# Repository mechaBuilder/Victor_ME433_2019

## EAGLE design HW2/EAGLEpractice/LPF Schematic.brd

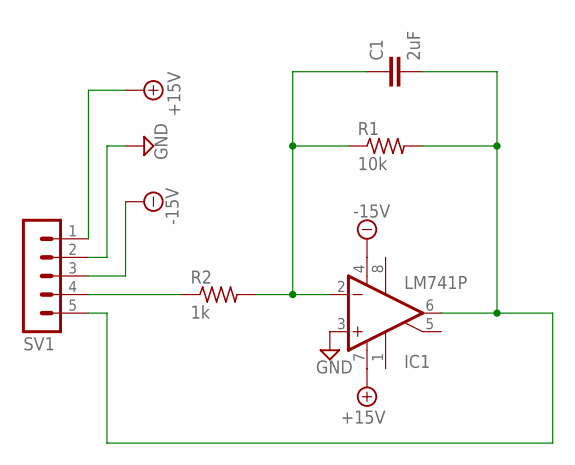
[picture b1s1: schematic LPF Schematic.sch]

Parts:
C1: 2uF; C0603
IC1: LM741P; DIL08
R1: 10k; R0603
R2: 1k; R0603
SV1: MA05-1

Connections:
+15V: IC1.7 (V+), SV1.1
-15V: IC1.4 (V-), SV1.3
GND: IC1.3 (+IN), SV1.2
unnamed: C1.1, IC1.2 (-IN), R1.1, R2.2
unnamed: C1.2, IC1.6 (OUT), R1.2, SV1.5
unnamed: R2.1, SV1.4

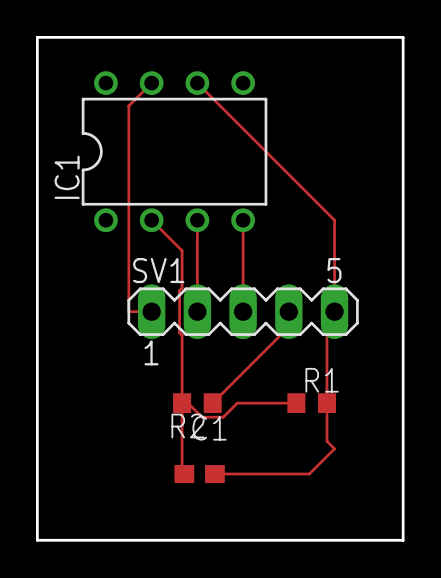
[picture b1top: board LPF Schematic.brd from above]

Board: 2 copper layers, 20.3 x 27.9 mm, 5 parts (0 on the bottom side), 6 nets.

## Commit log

2019-04-03 Create README.txt
    My first commit
2019-04-03 Update README.txt
    Another change
2019-04-03 Create PIC32MX1XX2XX-28-36-44-PIN-DS60001168K.pdf
    Added PIC32 datasheet
2019-04-03 Added data sheets
2019-04-03 added circuitDiagram
2019-04-03 regulator screenshots
2019-04-04 compleCircuit
2019-04-04 Created programming folder
2019-04-04 Added templace to main.c
2019-04-04 DEVCFG1 updated
2019-04-04 DEVCFG2 cofigured
2019-04-04 DEVCFG3 configured
2019-04-04 fixed error and programmed PIC
2019-04-04 Pushbutton added
2019-04-04 It works!
2019-04-04 Uploaded video
2019-04-04 README.md
2019-04-05 EAGLEpractice
2019-04-09 created EAGLE library
2019-04-09 schematic
2019-04-15 readme
2019-04-18 nonlinear
2019-04-23 HW4 complete
2019-04-23 HW5 initiated
2019-04-24 HW5 complete
2019-04-25 Added 5Hz Heartbeat
2019-04-25 Revised heartbeat location (PIC - not expander)
2019-04-25 added HW4 (SPI) schematic
2019-04-25 created HW6 folder & started coding
2019-04-25 nonlinear hw3
2019-04-25 hw3 nonlienar
2019-04-26 HW6: need to update (1) FPS & (2) progressBar flicker
2019-04-30 HW6, fixed bugs - progress bar and FPS
2019-04-30 added demo video
2019-05-01 created HW7 folder
2019-05-01 started coding: bugs in I2C comm
2019-05-01 Who Am I works, val 255 not 105.
2019-05-02 updated hw7, bugs: temp val doesnt make sense
2019-05-02 bug: the vals read from all registers are the same!
2019-05-02 fixed: accel data bug. PIC needed a hard restart
2019-05-07 bug: neg dir x and y doesnt work
2019-05-09 fixed bugs: signed char!!!!
2019-05-09 demo video added
2019-05-09 closed file
2019-05-09 created HW8 folder
2019-05-11 due to path errors, proj is saved to C:\microchip\harmony\v2_06\apps. After proj build, copied proj into HW8 repo.
2019-05-11 removed pragma warnings
2019-05-11 updated expander code
2019-05-11 created folder and started coding
2019-05-11 fixed heartbeat
2019-05-12 HW9 complete
2019-05-16 started HW11, need to complete HW10 to get vals to putty/Matlab
2019-05-16 HW10 completed
2019-05-18 3Dprinting&laserCutting complete
2019-05-18 playing w Ultimaker 3Dprinter
2019-05-22 app.c for hw11
2019-05-28 HW14 created - all object photos in folder
2019-05-31 hw11 complete, tranfered folder to repo
2019-06-02 hw12 folder transfered, assignment complete. Mouse. BOOM!
2019-06-03 cleaned folder
2019-06-03 PWM working; need image processing clarifications
2019-06-15 hw15: added camera fcn & hw16 : all files
2019-06-15 hw15 finished
2019-06-15 hw16 cad
2019-06-15 hw16 code & media
2019-06-15 hw16
2019-06-15 hw16 media
2019-06-15 hw11 updated video
